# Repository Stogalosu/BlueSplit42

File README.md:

# Bluesplit42
## What?(description)
Bluesplit42 is a split custom mechanical keyboard built entirely by me, except for the switches and keycaps. It will be a 40% layout with 42 keys, thus the 42 in the name.
It will have linear switches and pom jelly keycaps, because I've always wanted those but they were too expensive (now they're on sale). For the firmware, I'm using ZMK

## But Why?
Simply because i love mechanical keyboards. I just love them. Plus, this event is a great way to get a keyboard that would otherwise be very expensive for my budget. Did I mention I love keyboards?

**3D Render**

**Left PCB**

**Right PCB**

**Full PCB with mousebites**

**Wiring diagram for the left PCB**

**Wiring diagram for the right PCB**

**Bom table**
|Name                         |Unit Price|Shipping|Amount|Total Cost|Notes                              |Link                                                 |
|-----------------------------|----------|--------|------|----------|-----------------------------------|-----------------------------------------------------|
|Case                         |$0.00     |$0.00   |1     |$0.00     |3D Printed in-house                |No link                                              |
|Keycaps                      |$0.00     |$0.00   |1     |$0.00     |3D Printed in-house                |No link                                              |
|Gateron Milky Yellow Switches|$15.46    |$0.00   |1     |$15.46    |50pcs                              |https://www.aliexpress.com/item/1005006425450443.html|
|Hotswap Sockets              |$4.79     |$0.00   |1     |$4.79     |70pcs/Color: Type 1                |https://www.aliexpress.com/item/1005008954571807.html|
|Durock Stabiliers            |$2.45     |$7.87   |2     |$12.77    |Color: V3-2u Teal                  |https://www.aliexpress.com/item/1005002192386317.html|
|XIAO NRF52840 Microcontroller|$18.63    |$6.11   |2     |$43.37    |                                   |https://www.tme.eu/ro/details/seeed-102010448        |
|1N4148W-7-F Diodes           |$0.08     |$0.00   |50    |$4.14     |They come with the microcontrollers|https://www.tme.eu/ro/en/details/1n4148w-e3-08/smd-universal-diodes/vishay|
|AKY0386 Batteries            |$5.32     |$0.00   |2     |$10.64    |They come with the microcontrollers|https://www.tme.eu/ro/details/aky-lp403035           |
|PCB                          |$20.16    |$7.55   |1     |$27.71    |From JLCPCB                        |No link                                              |
|Total Cost                   |          |        |      |$118.88   |                                   |                                                     |

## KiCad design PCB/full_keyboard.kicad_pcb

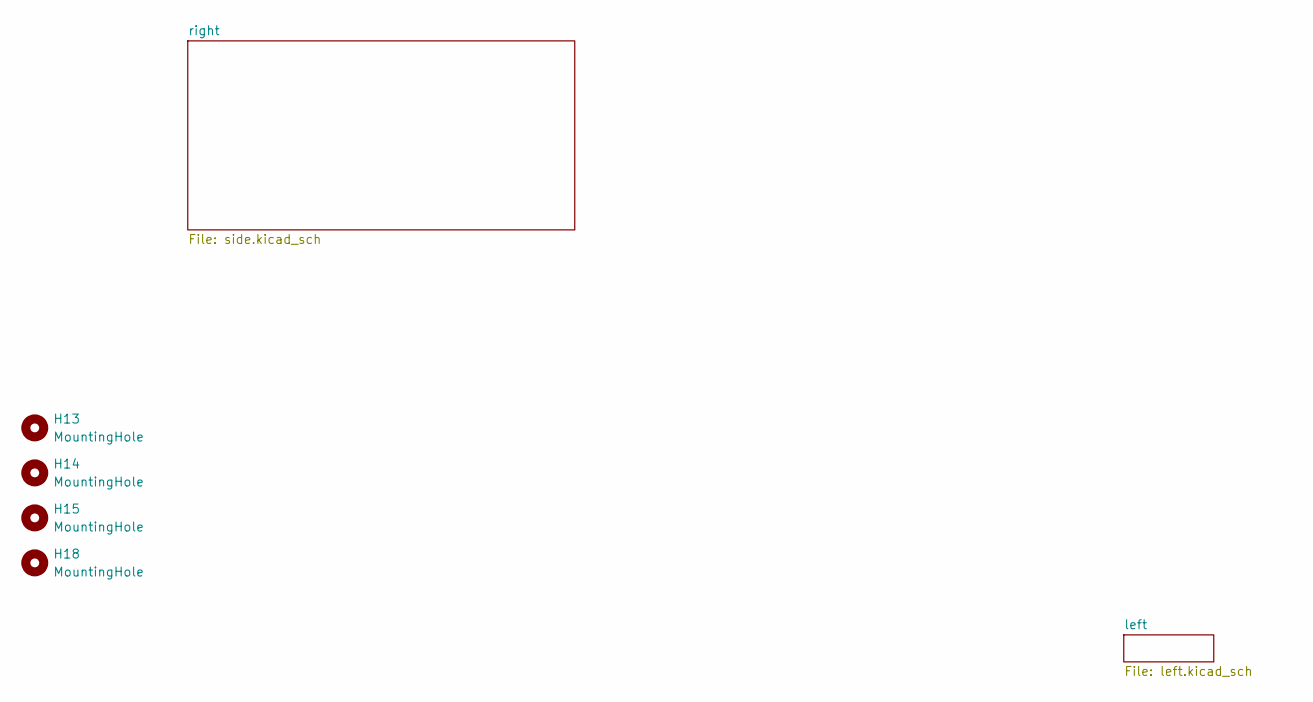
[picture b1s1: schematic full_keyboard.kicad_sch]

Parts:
H13, H14, H15, H18: MountingHole; mouse-bite-3mm-slot

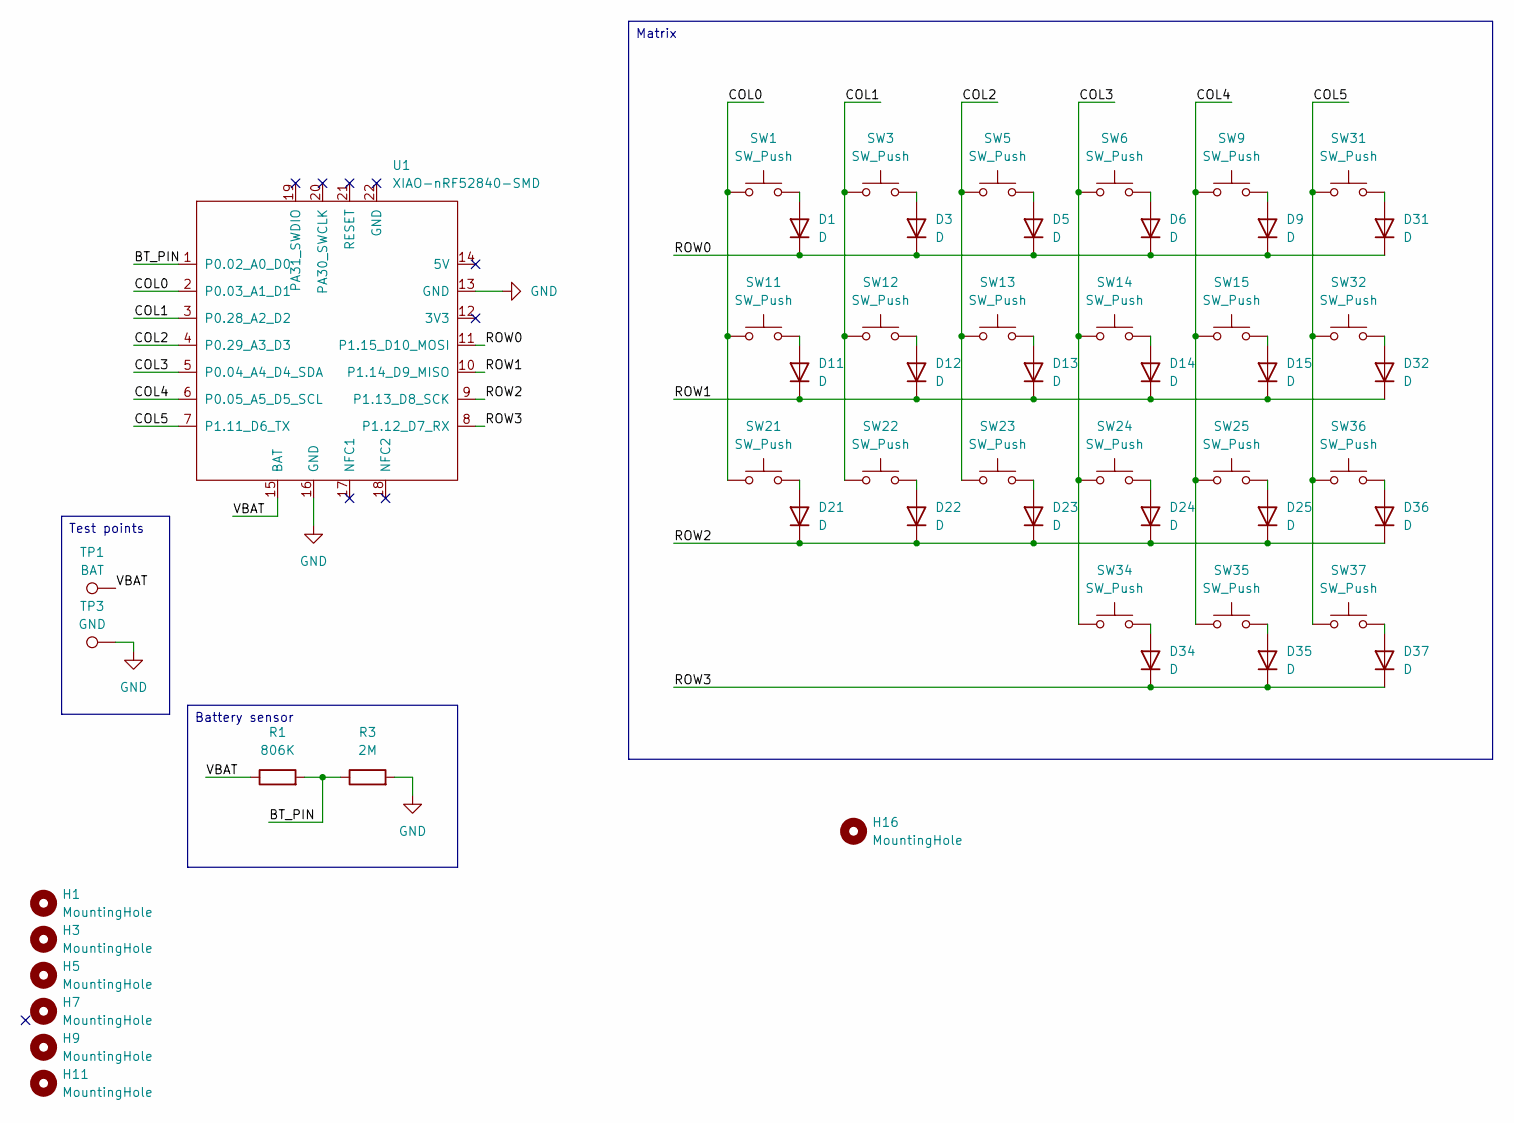
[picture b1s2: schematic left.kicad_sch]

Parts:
D1, D3, D5, D6, D9, D11, D12, D13, D14, D15, D21, D22, D23, D24, D25, D31, D32, D34, D35, D36, D37: D; D_SOD-123
H1, H3, H5, H7, H9, H11: MountingHole; MountingHole_2.2mm_M2
H16: MountingHole; Stabilizer_Cherry_MX_2.00u
R1: 806K; R_0805_2012Metric
R3: 2M; R_0805_2012Metric
SW1, SW3, SW5, SW6, SW9, SW11, SW12, SW13, SW14, SW15, SW21, SW22, SW23, SW24, SW25, SW31, SW32, SW34, SW35, SW36, SW37: SW_Push; SW_MX_HS_CPG151101S11_1u
TP1: BAT; TestPoint_Pad_D2.0mm
TP3: GND; TestPoint_Pad_D2.0mm
U1: XIAO-nRF52840-SMD; modified-XIAO-nRF52840-SMD

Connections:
/left/BT_PIN: R1.2, R3.1, U1.1 (P0.02_A0_D0)
/left/COL0: SW1.1, SW11.1, SW21.1, U1.2 (P0.03_A1_D1)
/left/COL1: SW3.1, SW12.1, SW22.1, U1.3 (P0.28_A2_D2)
/left/COL2: SW5.1, SW13.1, SW23.1, U1.4 (P0.29_A3_D3)
/left/COL3: SW6.1, SW14.1, SW24.1, SW34.1, U1.5 (P0.04_A4_D4_SDA)
/left/COL4: SW9.1, SW15.1, SW25.1, SW35.1, U1.6 (P0.05_A5_D5_SCL)
/left/COL5: SW31.1, SW32.1, SW36.1, SW37.1, U1.7 (P1.11_D6_TX)
/left/ROW0: D1.1 (K), D3.1 (K), D5.1 (K), D6.1 (K), D9.1 (K), D31.1 (K), U1.11 (P1.15_D10_MOSI)
/left/ROW1: D11.1 (K), D12.1 (K), D13.1 (K), D14.1 (K), D15.1 (K), D32.1 (K), U1.10 (P1.14_D9_MISO)
/left/ROW2: D21.1 (K), D22.1 (K), D23.1 (K), D24.1 (K), D25.1 (K), D36.1 (K), U1.9 (P1.13_D8_SCK)
/left/ROW3: D34.1 (K), D35.1 (K), D37.1 (K), U1.8 (P1.12_D7_RX)
/left/VBAT: R1.1, TP1.1, U1.15 (BAT)
GND: R3.2, TP3.1, U1.13 (GND), U1.16 (GND); also elsewhere on the board
unnamed: D1.2 (A), SW1.2
unnamed: D3.2 (A), SW3.2
unnamed: D5.2 (A), SW5.2
unnamed: D6.2 (A), SW6.2
unnamed: D9.2 (A), SW9.2
unnamed: D11.2 (A), SW11.2
unnamed: D12.2 (A), SW12.2
unnamed: D13.2 (A), SW13.2
unnamed: D14.2 (A), SW14.2
unnamed: D15.2 (A), SW15.2
unnamed: D21.2 (A), SW21.2
unnamed: D22.2 (A), SW22.2
unnamed: D23.2 (A), SW23.2
unnamed: D24.2 (A), SW24.2
unnamed: D25.2 (A), SW25.2
unnamed: D31.2 (A), SW31.2
unnamed: D32.2 (A), SW32.2
unnamed: D34.2 (A), SW34.2
unnamed: D35.2 (A), SW35.2
unnamed: D36.2 (A), SW36.2
unnamed: D37.2 (A), SW37.2

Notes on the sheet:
Matrix
Test points
Battery sensor

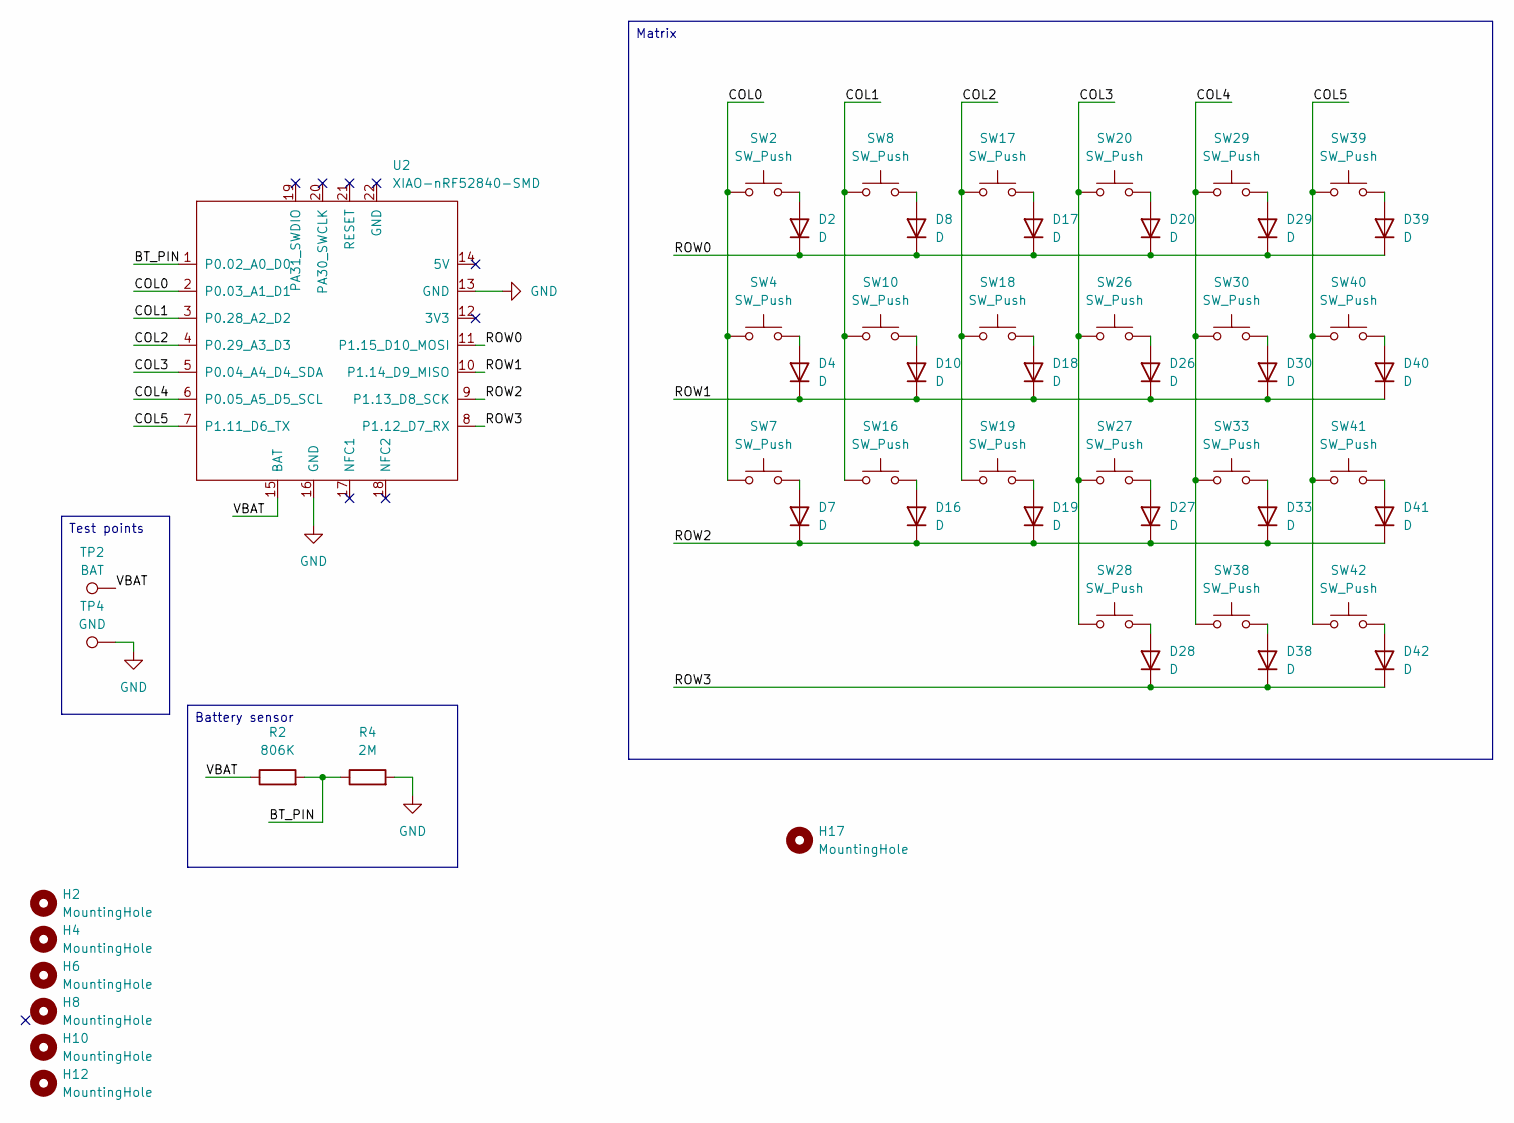
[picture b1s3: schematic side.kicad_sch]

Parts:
D2, D4, D7, D8, D10, D16, D17, D18, D19, D20, D26, D27, D28, D29, D30, D33, D38, D39, D40, D41, D42: D; D_SOD-123
H2, H4, H6, H8, H10, H12: MountingHole; MountingHole_2.2mm_M2
H17: MountingHole; Stabilizer_Cherry_MX_2.00u
R2: 806K; R_0805_2012Metric
R4: 2M; R_0805_2012Metric
SW2, SW4, SW7: SW_Push; SW_MX_HS_CPG151101S11_1.25u
SW8, SW10, SW16, SW17, SW18, SW19, SW20, SW26, SW27, SW28, SW29, SW30, SW33, SW38, SW39, SW40, SW41, SW42: SW_Push; SW_MX_HS_CPG151101S11_1u
TP2: BAT; TestPoint_Pad_D2.0mm
TP4: GND; TestPoint_Pad_D2.0mm
U2: XIAO-nRF52840-SMD; modified-XIAO-nRF52840-SMD

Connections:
/right/BT_PIN: R2.2, R4.1, U2.1 (P0.02_A0_D0)
/right/COL0: SW2.1, SW4.1, SW7.1, U2.2 (P0.03_A1_D1)
/right/COL1: SW8.1, SW10.1, SW16.1, U2.3 (P0.28_A2_D2)
/right/COL2: SW17.1, SW18.1, SW19.1, U2.4 (P0.29_A3_D3)
/right/COL3: SW20.1, SW26.1, SW27.1, SW28.1, U2.5 (P0.04_A4_D4_SDA)
/right/COL4: SW29.1, SW30.1, SW33.1, SW38.1, U2.6 (P0.05_A5_D5_SCL)
/right/COL5: SW39.1, SW40.1, SW41.1, SW42.1, U2.7 (P1.11_D6_TX)
/right/ROW0: D2.1 (K), D8.1 (K), D17.1 (K), D20.1 (K), D29.1 (K), D39.1 (K), U2.11 (P1.15_D10_MOSI)
/right/ROW1: D4.1 (K), D10.1 (K), D18.1 (K), D26.1 (K), D30.1 (K), D40.1 (K), U2.10 (P1.14_D9_MISO)
/right/ROW2: D7.1 (K), D16.1 (K), D19.1 (K), D27.1 (K), D33.1 (K), D41.1 (K), U2.9 (P1.13_D8_SCK)
/right/ROW3: D28.1 (K), D38.1 (K), D42.1 (K), U2.8 (P1.12_D7_RX)
/right/VBAT: R2.1, TP2.1, U2.15 (BAT)
GND: R4.2, TP4.1, U2.13 (GND), U2.16 (GND); also elsewhere on the board
unnamed: D2.2 (A), SW2.2
unnamed: D4.2 (A), SW4.2
unnamed: D7.2 (A), SW7.2
unnamed: D8.2 (A), SW8.2
unnamed: D10.2 (A), SW10.2
unnamed: D16.2 (A), SW16.2
unnamed: D17.2 (A), SW17.2
unnamed: D18.2 (A), SW18.2
unnamed: D19.2 (A), SW19.2
unnamed: D20.2 (A), SW20.2
unnamed: D26.2 (A), SW26.2
unnamed: D27.2 (A), SW27.2
unnamed: D28.2 (A), SW28.2
unnamed: D29.2 (A), SW29.2
unnamed: D30.2 (A), SW30.2
unnamed: D33.2 (A), SW33.2
unnamed: D38.2 (A), SW38.2
unnamed: D39.2 (A), SW39.2
unnamed: D40.2 (A), SW40.2
unnamed: D41.2 (A), SW41.2
unnamed: D42.2 (A), SW42.2

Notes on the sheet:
Matrix
Test points
Battery sensor

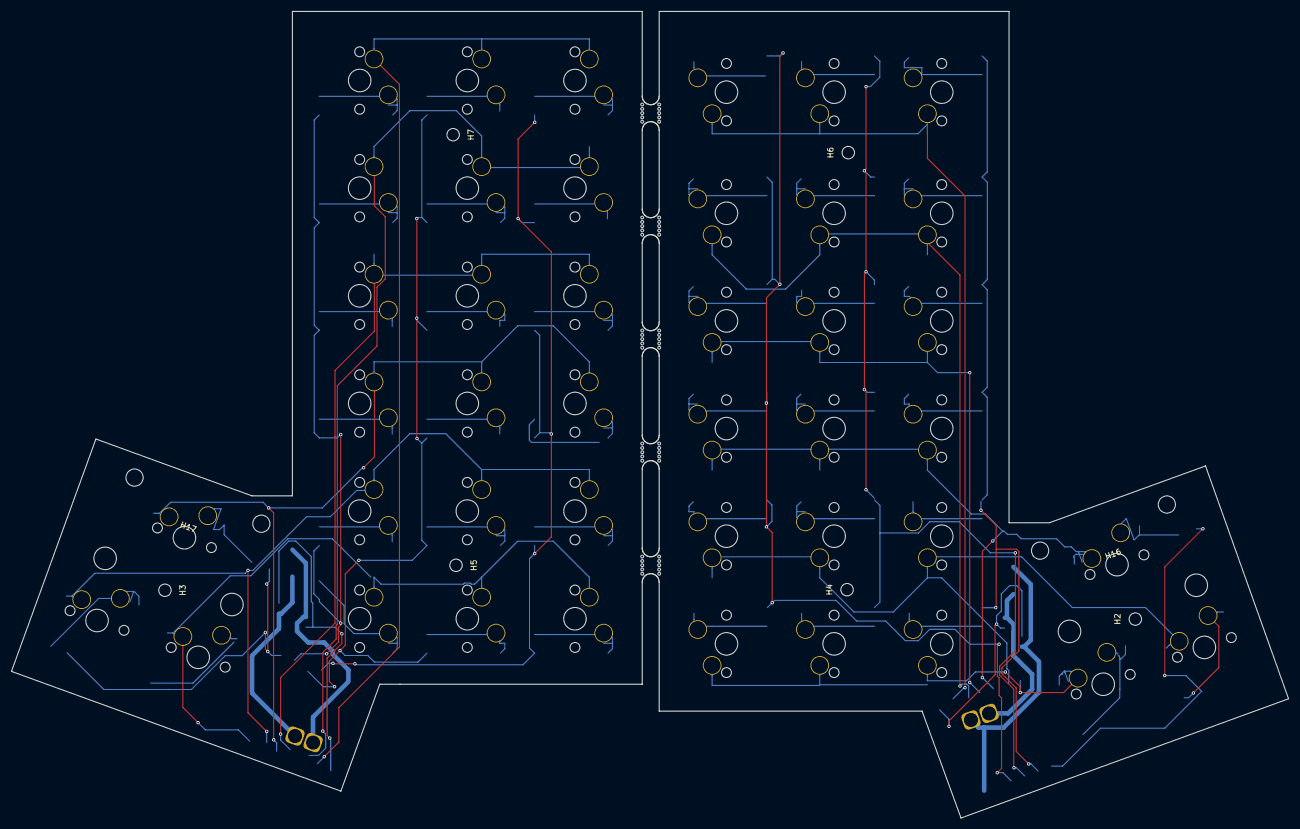
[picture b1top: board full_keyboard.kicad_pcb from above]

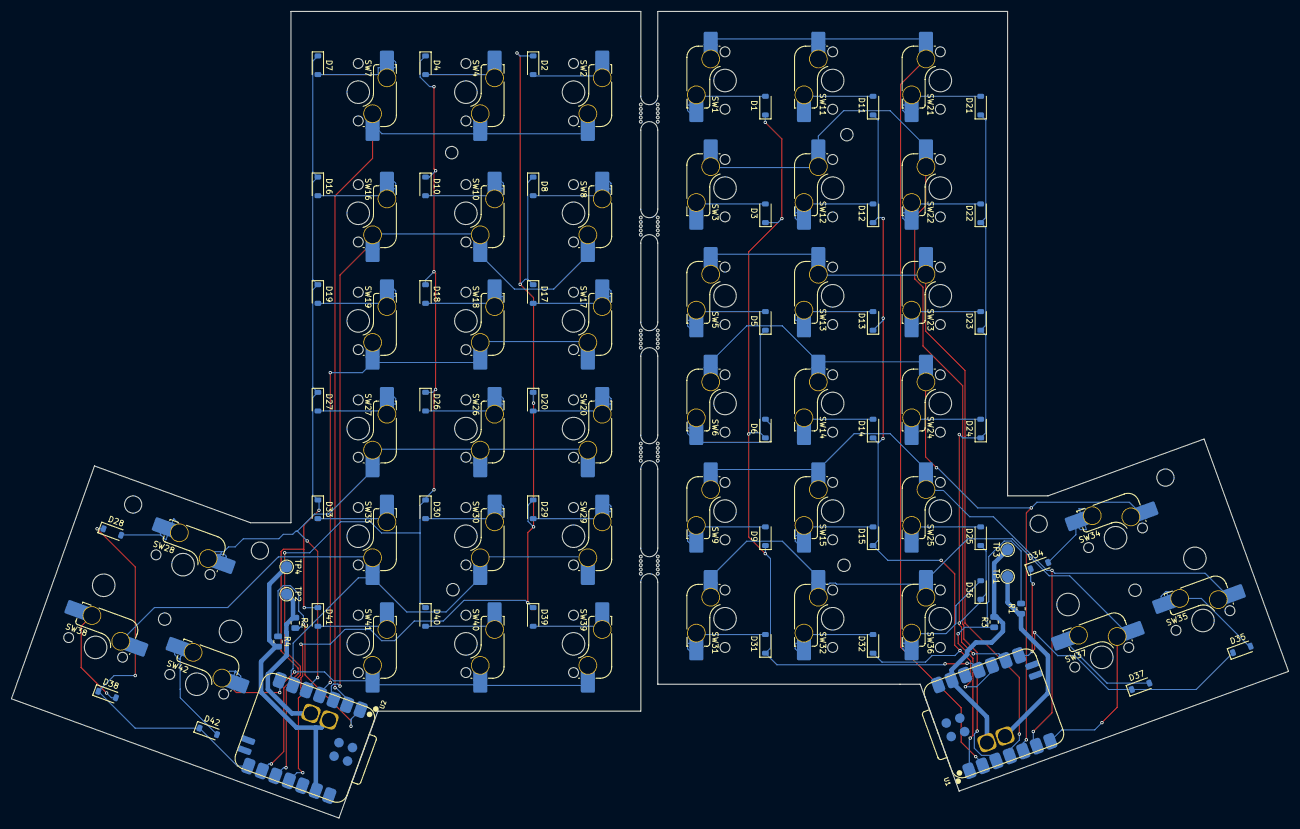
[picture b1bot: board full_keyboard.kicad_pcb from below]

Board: 2 copper layers, 226.0 x 142.7 mm, 107 parts (94 on the bottom side), 67 nets.

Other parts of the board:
H19, H20, H21, H22: MountingHole; mouse-bite-3mm-slot

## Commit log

2025-11-10 Update README with project details for Bluesplit42
    Added detailed description of the Bluesplit42 keyboard project.
2025-11-10 Enhance README formatting and add PCB images
    Updated README.md to improve formatting and add images.
2025-11-14 Insert 3D render image in README
    Added a 3D render image to the README.
2025-11-15 Added BOM.csv file
2025-11-15 Added 3D model files
2025-11-15 Create PCB
2025-11-16 Revise README structure and add BOM table
2025-11-16 Added project files
2025-11-16 Rename full_keyboard.kicad_pro file
2025-11-16 Modified diodes link in CSV
2025-11-18 Update PCB cost and total cost in README
2025-11-18 Update note on full PCB cost in README
    Clarified note about the full PCB with mousebites being more expensive than purchasing two separate PCBs.
2025-11-18 Clarify note about full PCB pricing
2025-11-19 Update PCB details and total cost in README
2025-11-19 Revise component prices and total cost in BOM.csv
    Updated prices and shipping costs for components in BOM.
2025-11-27 Updated gerber files to include drill files
